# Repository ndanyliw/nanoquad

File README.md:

nanoquad
========

A low cost quadcopter development platform

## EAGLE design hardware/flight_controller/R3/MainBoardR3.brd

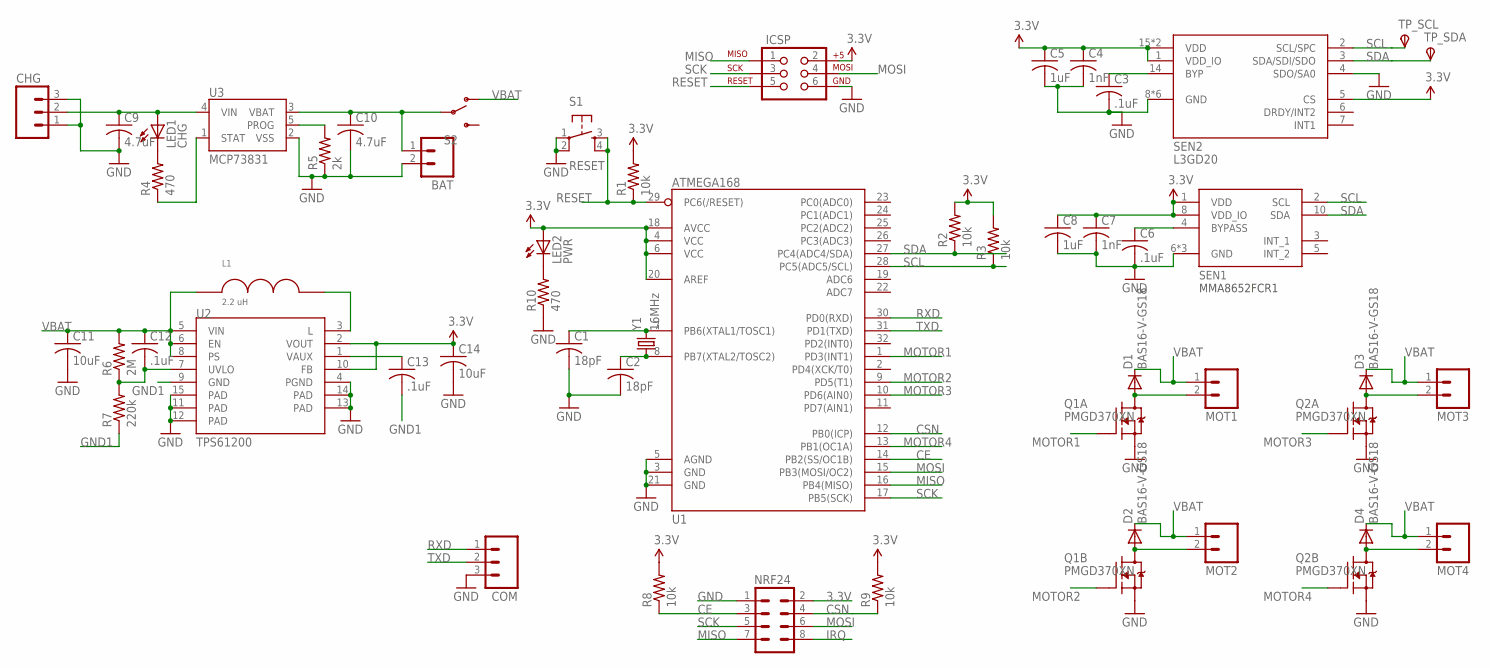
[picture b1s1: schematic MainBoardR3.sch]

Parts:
BAT: M02LOCK_LONGPADS; 1X02_LOCK_LONGPADS
C1, C2: 18pF; C0805
C3, C6, C12, C13: .1uF; C0805
C4, C7: 1nF; C0805
C5, C8: 1uF; C0805
C9, C10: 4.7uF; C0805
C11, C14: 10uF; C0805
CHG: M03LONGPADS; 1X03_LONGPADS
COM: M03LONGPADS; 1X03_LONGPADS
D1, D2, D3, D4: BAS16-V-GS18; SOT23
ICSP: AVR_SPI_PRG_62X3_LOCK; 2X3_LOCK
L1: 2.2 uH; 2518
LED1: CHG; LED-1206
LED2: PWR; LED-1206
MOT1, MOT2, MOT3, MOT4: M02LOCK_LONGPADS; 1X02_LOCK_LONGPADS
NRF24: M04X2; 2X4
Q1, Q2: PMGD370XN; SOT363_INFINEON
R1, R2, R3, R8, R9: 10k; 0805
R4, R10: 470; 0805
R5: 2k; 0805
R6: 2M; 0805
R7: 220k; 0805
S1: RESET; TACTILE_SWITCH_SMD
S2: SWITCH-SPST-SMD-A
SEN1: MMA8652FCR1; 10_PIN_DFN
SEN2: L3GD20; LGA-16
TP_SCL: TPSTP14SQ; TP14SQ
TP_SDA: TPSTP14SQ; TP14SQ
U1: ATMEGA168; TQFP32-08
U2: TPS61200; QFN-10_PAD
U3: MCP73831; SOT23-5
Y1: 16MHz; CRYSTAL-SMD-10.5X4.8-2PIN

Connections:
3.3V: C4.1, C5.1, C7.1, C8.1, C14.1, ICSP.2, LED2.A, NRF24.2, R1.2, R2.2, R3.2, R8.2, R9.2, SEN1.1 (VDD), SEN1.8 (VDD_IO), SEN2.1 (VDD_IO), SEN2.5 (CS), SEN2.15 (VDD), SEN2.16 (VDD), U1.4 (VCC), U1.6 (VCC), U1.18 (AVCC), U1.20 (AREF), U2.2 (VOUT), U2.10 (FB)
BAT+: BAT.1, C10.1, S2.2, U3.3 (VBAT)
CE: NRF24.3, R8.1, U1.14 (PB2(SS/OC1B))
CSN: NRF24.4, R9.1, U1.12 (PB0(ICP))
GND: BAT.2, C1.2, C2.2, C3.2, C4.2, C5.2, C6.2, C7.2, C8.2, C9.2, C10.2, C11.2, C14.2, CHG.1, CHG.3, COM.3, ICSP.6, NRF24.1, Q1.1 (S), Q1.4 (S), Q2.1 (S), Q2.4 (S), R5.1, R10.1, S1.1, S1.2, SEN1.6 (GND), SEN1.7 (GND), SEN1.9 (GND), SEN2.4 (SDO/SA0), SEN2.8 (GND), SEN2.9 (GND), SEN2.10 (GND), SEN2.11 (GND), SEN2.12 (GND), SEN2.13 (GND), U1.3 (GND), U1.5 (AGND), U1.21 (GND), U2.4 (PGND), U2.11 (PAD), U2.12 (PAD), U2.13 (PAD), U2.14 (PAD), U2.15 (PAD), U3.2 (VSS)
GND1: C13.2, R7.1, U2.9 (GND)
IRQ: NRF24.8
MISO: ICSP.1, NRF24.7, U1.16 (PB4(MISO))
MOSI: ICSP.4, NRF24.6, U1.15 (PB3(MOSI/OC2))
MOT1-: D1.1 (A), MOT1.2, Q1.6 (D)
MOT2-: D2.1 (A), MOT2.2, Q1.3 (D)
MOT3-: D3.1 (A), MOT3.2, Q2.6 (D)
MOT4-: D4.1 (A), MOT4.2, Q2.3 (D)
MOTOR1: Q1.2 (G), U1.1 (PD3(INT1))
MOTOR2: Q1.5 (G), U1.9 (PD5(T1))
MOTOR3: Q2.2 (G), U1.10 (PD6(AIN0))
MOTOR4: Q2.5 (G), U1.13 (PB1(OC1A))
unnamed: C3.1, SEN2.14 (BYP)
unnamed: C1.1, U1.7 (PB6(XTAL1/TOSC1)), Y1.P$2 (2)
unnamed: C2.1, U1.8 (PB7(XTAL2/TOSC2)), Y1.P$1 (1)
unnamed: LED1.C, R4.2
unnamed: C6.1, SEN1.4 (BYPASS)
unnamed: R4.1, U3.1 (STAT)
unnamed: R5.2, U3.5 (PROG)
unnamed: C13.1, U2.1 (VAUX)
unnamed: C12.2, R6.1, R7.2, U2.7 (UVLO)
unnamed: LED2.C, R10.2
unnamed: L1.P$2 (2), U2.3 (L)
RESET: ICSP.5, R1.1, S1.3, S1.4, U1.29 (PC6(/RESET))
RXD: COM.1, U1.30 (PD0(RXD))
SCK: ICSP.3, NRF24.5, U1.17 (PB5(SCK))
SCL: R3.1, SEN1.2 (SCL), SEN2.2 (SCL/SPC), TP_SCL.TP, U1.28 (PC5(ADC5/SCL))
SDA: R2.1, SEN1.10 (SDA), SEN2.3 (SDA/SDI/SDO), TP_SDA.TP, U1.27 (PC4(ADC4/SDA))
TXD: COM.2, U1.31 (PD1(TXD))
VBAT: C11.1, C12.1, D1.3 (C), D2.3 (C), D3.3 (C), D4.3 (C), L1.P$1 (1), MOT1.1, MOT2.1, MOT3.1, MOT4.1, R6.2, S2.1 (O), U2.5 (VIN), U2.6 (EN), U2.8 (PS)
VIN: C9.1, CHG.2, LED1.A, U3.4 (VIN)

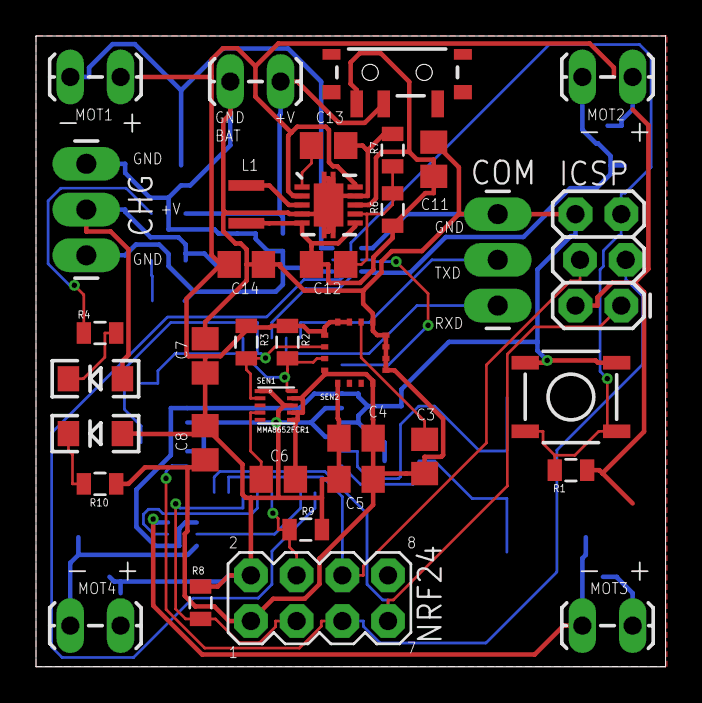
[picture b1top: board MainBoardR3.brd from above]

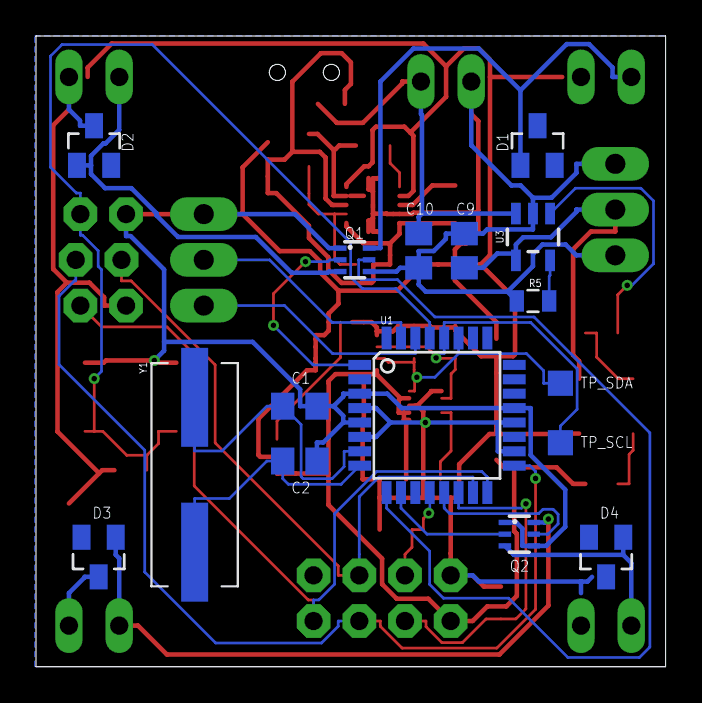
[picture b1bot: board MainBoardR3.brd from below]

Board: 2 copper layers, 35.0 x 35.0 mm, 52 parts (16 on the bottom side), 35 nets.

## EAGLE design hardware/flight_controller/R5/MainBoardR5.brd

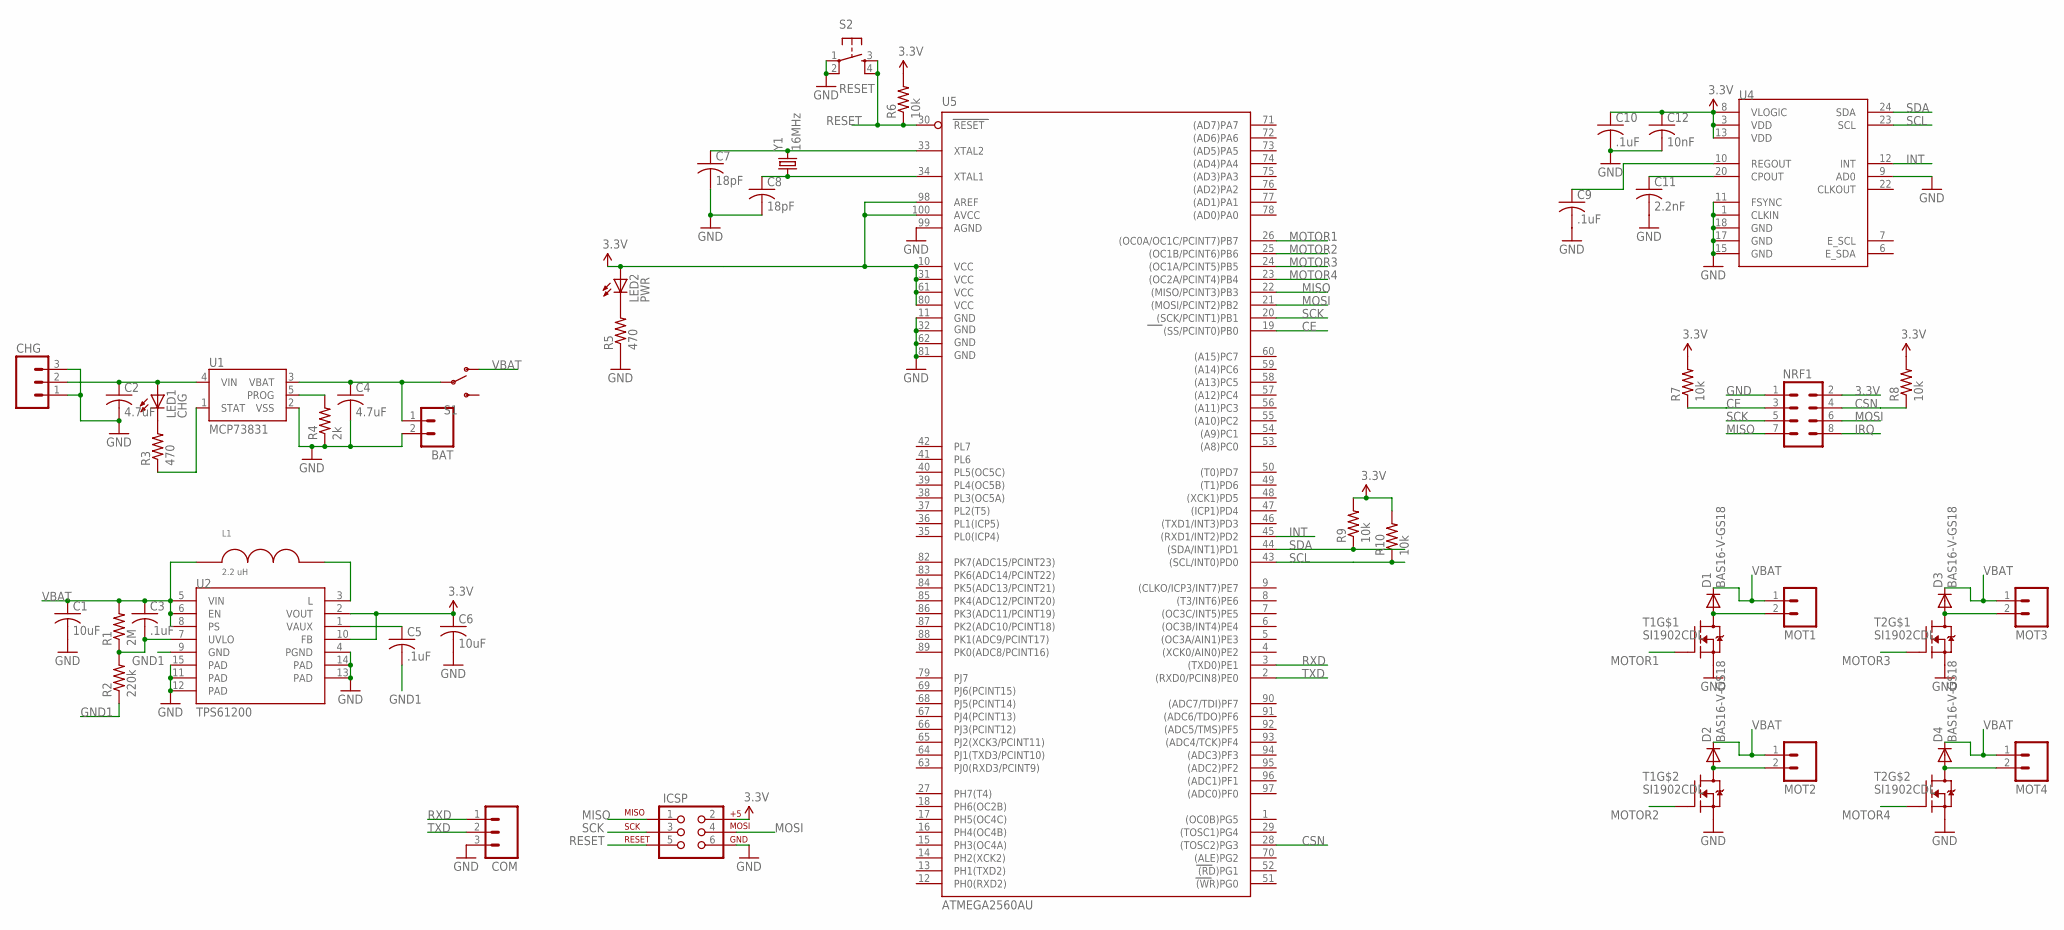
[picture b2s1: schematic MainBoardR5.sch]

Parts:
BAT: M02LOCK_LONGPADS; 1X02_LOCK_LONGPADS
C1, C6: 10uF; C0805
C2, C4: 4.7uF; C0805
C3, C5, C9, C10: .1uF; C0805
C7, C8: 18pF; C0805
C11: 2.2nF; C0805
C12: 10nF; C0805
CHG: M03LONGPADS; 1X03_LONGPADS
COM: M03LONGPADS; 1X03_LONGPADS
D1, D2, D3, D4: BAS16-V-GS18; SOT23
ICSP: AVR_SPI_PRG_62X3_LOCK; 2X3_LOCK
L1: 2.2 uH; 2518
LED1: CHG; LED-1206
LED2: PWR; LED-1206
MOT1, MOT2, MOT3, MOT4: M02LOCK_LONGPADS; 1X02_LOCK_LONGPADS
NRF1: M04X2; 2X4
R1: 2M; 0805
R2: 220k; 0805
R3, R5: 470; 0805
R4: 2k; 0805
R6, R7, R8, R9, R10: 10k; 0805
S1: SWITCH-SPST-SMD-A
S2: RESET; TACTILE_SWITCH_SMD
T1, T2: SI1902CDL; SOT363_INFINEON
U1: MCP73831; SOT23-5
U2: TPS61200; QFN-10_PAD
U4: MPU-9150QFN-24-NP; QFN-24-NP
U5: ATMEGA2560AU; TQFP100
Y1: 16MHz; CRYSTAL-SMD-5X3

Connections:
3.3V: C6.1, C10.1, C12.1, ICSP.2, LED2.A, NRF1.2, R6.2, R7.2, R8.2, R9.2, R10.2, U2.2 (VOUT), U2.10 (FB), U4.3 (VDD), U4.8 (VLOGIC), U4.13 (VDD), U5.10 (VCC), U5.31 (VCC1), U5.61 (VCC2), U5.80 (VCC3), U5.98 (AREF), U5.100 (AVCC)
BAT+: BAT.1, C4.1, S1.2, U1.3 (VBAT)
CE: NRF1.3, R7.1, U5.19 ((SS/PCINT0)PB0)
CSN: NRF1.4, R8.1, U5.28 ((TOSC2)PG3)
GND: BAT.2, C1.2, C2.2, C4.2, C6.2, C7.2, C8.2, C9.2, C10.2, C11.2, C12.2, CHG.1, CHG.3, COM.3, ICSP.6, NRF1.1, R4.1, R5.1, S2.1, S2.2, T1.1 (S), T1.4 (S), T2.1 (S), T2.4 (S), U1.2 (VSS), U2.4 (PGND), U2.11 (PAD), U2.12 (PAD), U2.13 (PAD), U2.14 (PAD), U2.15 (PAD), U4.1 (CLKIN), U4.9 (AD0), U4.11 (FSYNC), U4.15 (GND), U4.17 (GND), U4.18 (GND), U5.11 (GND), U5.32 (GND1), U5.62 (GND2), U5.81 (GND3), U5.99 (AGND)
GND1: C5.2, R2.1, U2.9 (GND)
INT: U4.12 (INT), U5.45 ((RXD1/INT2)PD2)
IRQ: NRF1.8
MISO: ICSP.1, NRF1.7, U5.22 ((MISO/PCINT3)PB3)
MOSI: ICSP.4, NRF1.6, U5.21 ((MOSI/PCINT2)PB2)
MOT1-: D1.1 (A), MOT1.2, T1.6 (D)
MOT2-: D2.1 (A), MOT2.2, T1.3 (D)
MOT3-: D3.1 (A), MOT3.2, T2.6 (D)
MOT4-: D4.1 (A), MOT4.2, T2.3 (D)
MOTOR1: T1.2 (G), U5.26 ((OC0A/OC1C/PCINT7)PB7)
MOTOR2: T1.5 (G), U5.25 ((OC1B/PCINT6)PB6)
MOTOR3: T2.2 (G), U5.24 ((OC1A/PCINT5)PB5)
MOTOR4: T2.5 (G), U5.23 ((OC2A/PCINT4)PB4)
unnamed: C7.1, U5.33 (XTAL2), Y1.3 (2)
unnamed: C8.1, U5.34 (XTAL1), Y1.1
unnamed: C11.1, U4.20 (CPOUT)
unnamed: LED1.C, R3.2
unnamed: C9.1, U4.10 (REGOUT)
unnamed: R3.1, U1.1 (STAT)
unnamed: R4.2, U1.5 (PROG)
unnamed: C5.1, U2.1 (VAUX)
unnamed: C3.2, R1.1, R2.2, U2.7 (UVLO)
unnamed: LED2.C, R5.2
unnamed: L1.P$2 (2), U2.3 (L)
RESET: ICSP.5, R6.1, S2.3, S2.4, U5.30 (RESET)
RXD: COM.1, U5.3 ((TXD0)PE1)
SCK: ICSP.3, NRF1.5, U5.20 ((SCK/PCINT1)PB1)
SCL: R10.1, U4.23 (SCL), U5.43 ((SCL/INT0)PD0)
SDA: R9.1, U4.24 (SDA), U5.44 ((SDA/INT1)PD1)
TXD: COM.2, U5.2 ((RXD0/PCIN8)PE0)
VBAT: C1.1, C3.1, D1.3 (C), D2.3 (C), D3.3 (C), D4.3 (C), L1.P$1 (1), MOT1.1, MOT2.1, MOT3.1, MOT4.1, R1.2, S1.1 (O), U2.5 (VIN), U2.6 (EN), U2.8 (PS)
VIN: C2.1, CHG.2, LED1.A, U1.4 (VIN)

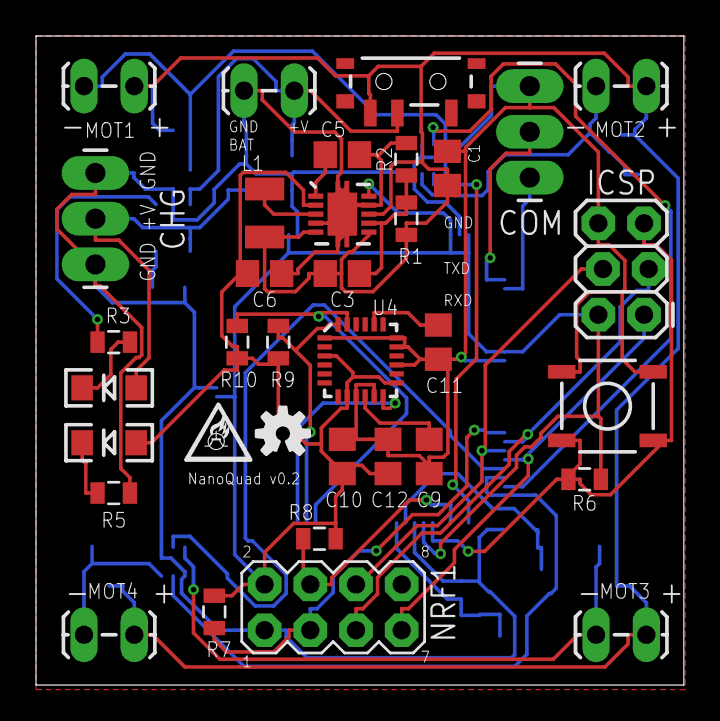
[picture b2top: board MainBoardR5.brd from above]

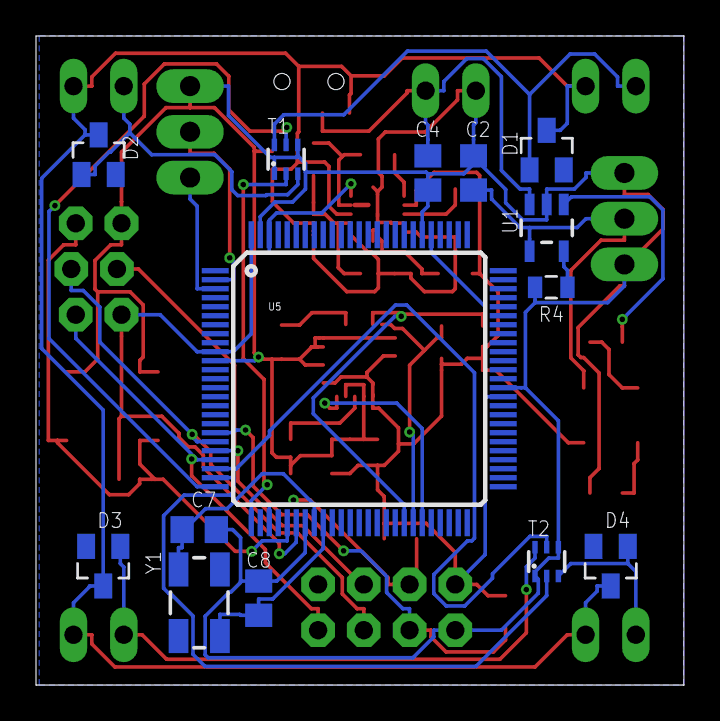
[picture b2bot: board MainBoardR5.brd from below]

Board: 2 copper layers, 36.0 x 36.1 mm, 49 parts (14 on the bottom side), 36 nets.

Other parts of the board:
U$1: BURNT_TRANSISTORS_XSM
U$2: OSHW-LOGO-S

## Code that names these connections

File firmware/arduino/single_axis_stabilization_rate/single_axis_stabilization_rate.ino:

/*
The MIT License (MIT)

Copyright (c) 2014 Ned Danyliw

Permission is hereby granted, free of charge, to any person obtaining a copy
of this software and associated documentation files (the "Software"), to deal
in the Software without restriction, including without limitation the rights
to use, copy, modify, merge, publish, distribute, sublicense, and/or sell
copies of the Software, and to permit persons to whom the Software is
furnished to do so, subject to the following conditions:

The above copyright notice and this permission notice shall be included in all
copies or substantial portions of the Software.

THE SOFTWARE IS PROVIDED "AS IS", WITHOUT WARRANTY OF ANY KIND, EXPRESS OR
IMPLIED, INCLUDING BUT NOT LIMITED TO THE WARRANTIES OF MERCHANTABILITY,
FITNESS FOR A PARTICULAR PURPOSE AND NONINFRINGEMENT. IN NO EVENT SHALL THE
AUTHORS OR COPYRIGHT HOLDERS BE LIABLE FOR ANY CLAIM, DAMAGES OR OTHER
LIABILITY, WHETHER IN AN ACTION OF CONTRACT, TORT OR OTHERWISE, ARISING FROM,
OUT OF OR IN CONNECTION WITH THE SOFTWARE OR THE USE OR OTHER DEALINGS IN THE
SOFTWARE.
*/

/*
This program runs a single axis stabilization algorithm on the quadcopter.
It only stabilizes in pitch.
*/

#include <stdlib.h>
#include <avr/io.h>
#include <avr/interrupt.h>
#include <avr/pgmspace.h>
#include <util/delay.h>
#include <math.h>  //include libm

#define UART_BAUD_RATE 57600
#include "mpu6050.h"
#include "mpu6050registers.h"
#include "i2cmaster.h"

#include <Wire.h>
#include "PID_v1.h"


#define MOTOR1 3
#define MOTOR2 5
#define MOTOR3 6
#define MOTOR4 9

#define XGYRO_OFFSET 16
#define YGYRO_OFFSET 16
#define ZGYRO_OFFSET 11


long *ptr = 0;
double qw = 1.0f;
double qx = 0.0f;
double qy = 0.0f;
double qz = 0.0f;
double roll = 0.0f;
double pitch = 0.0f;
double yaw = 0.0f;

double pitch_deg, roll_deg, yaw_deg;

int16_t mx = 0;
int16_t my = 0;
int16_t mz = 0;

int16_t gx, gy, gz;

double pitch_setpoint = 0.0f;
uint8_t thrust = 200;

int motor1, motor2, motor3, motor4;

double pitch_error;
double pitch_error_sum = 0.0f;

double pitch_rate;
double gyro_pitch_rate;

double kp_pitch_att = 4;
double ki_pitch_att = 0.05;
double kd_pitch_att = 0.0;

double kp_pitch_rate = .4;
double ki_pitch_rate = 0.005;
double kd_pitch_rate = 0.0;

double error;

long last = 0;
long time_elapsed;

//create PID controllers for pitch
PID pitch_pid_attitude(&pitch_deg, &pitch_error, &pitch_setpoint, kp_pitch_att, ki_pitch_att, kd_pitch_att, DIRECT);
PID pitch_pid_rate(&gyro_pitch_rate, &pitch_rate, &pitch_error, kp_pitch_rate, ki_pitch_rate, kd_pitch_rate, DIRECT);

void setup() {
    //set up 8 bit Fast PWM
    TCCR2A = _BV(COM2A1) | _BV(COM2B1) | _BV(WGM21) | _BV(WGM20);
    TCCR1A = _BV(COM1A1) | _BV(COM1B1) | _BV(WGM10);
    TCCR1B = _BV(WGM12) | _BV(CS11) | _BV(CS10);

    //zero motors
    analogWrite(MOTOR1, 0);
    analogWrite(MOTOR3, 0);
    analogWrite(MOTOR2, 0);
    analogWrite(MOTOR4, 0);

    Wire.begin();
    Serial.begin(UART_BAUD_RATE);

    //init mpu6050
    mpu6050_init();
    delay(50);

    mpu6050_setXGyroOffset(XGYRO_OFFSET);
    mpu6050_setYGyroOffset(YGYRO_OFFSET);
    mpu6050_setZGyroOffset(ZGYRO_OFFSET);

    mpu6050_dmpInitialize();
    mpu6050_dmpEnable();
    delay(10);

    //get gyro reading
    mpu6050_getRawGyro(&gx, &gy, &gz);

    //initialize PID
    pitch_pid_attitude.SetSampleTime(50);
    pitch_pid_attitude.SetOutputLimits(-180, 180);

    pitch_pid_rate.SetSampleTime(50);
    pitch_pid_rate.SetOutputLimits(-255+thrust, 255-thrust);

    delay(5000);
    last = millis();
    pitch_deg = -pitch * 180.0/3.1416;
    gyro_pitch_rate = (gx - XGYRO_OFFSET)/MPU6050_GYRO_LSB_2000;
    pitch_pid_attitude.SetMode(AUTOMATIC);
    pitch_pid_rate.SetMode(AUTOMATIC);
}

void loop() {
    time_elapsed = millis();
    if(mpu6050_getQuaternionWait(&qw, &qx, &qy, &qz)) {
        mpu6050_getRollPitchYaw(qw, qx, qy, qz, &roll, &pitch, &yaw);
    }
    // read_compass(&mx, &my, &mz);
    // uart_puts("hello world4!\n");

    mpu6050_getRawGyro(&gx, &gy, &gz);
    pitch_deg = -pitch * 180.0/3.1416;
    gyro_pitch_rate = (gx - XGYRO_OFFSET)/MPU6050_GYRO_LSB_2000;

    // error = pitch_setpoint - pitch;
    // pitch_error_sum += error * (millis() - last)/1000.0;
    // pitch_error = kp_pitch*error + ki_pitch * pitch_error_sum;
    // last = millis();

    pitch_pid_attitude.Compute();
    pitch_pid_rate.Compute();

    //assign values to motors
    motor1 = thrust + pitch_rate;
    motor2 = thrust + pitch_rate;
    motor3 = thrust - pitch_rate;
    motor4 = thrust - pitch_rate;

    //handle overflow
    if (motor1 < 0) {
        motor1 = 0;
    } else if (motor1 > 255) {
        motor1 = 255;
    }

    if (motor2 < 0) {
        motor2 = 0;
    } else if (motor2 > 255) {
        motor2 = 255;
    }

    if (motor3 < 0) {
        motor3 = 0;
    } else if (motor3 > 255) {
        motor3 = 255;
    }

    if (motor4 < 0) {
        motor4 = 0;
    } else if (motor4 > 255) {
        motor4 = 255;
    }

    // analogWrite(MOTOR1, 0);
    // analogWrite(MOTOR3, 0);
    // analogWrite(MOTOR2, 0);
    // analogWrite(MOTOR4, 0);

    // if (millis() - last > 500) {
    //     Serial.print("Pitch - ");
    //     Serial.println(pitch_deg);
    //     Serial.print("Pitch Rate - ");
    //     Serial.println(gyro_pitch_rate);
    //     Serial.print("Motor 1 - ");
    //     Serial.println(motor1);
    //     Serial.print("Motor 3 - ");
    //     Serial.println(motor3);
    //     Serial.println(millis() - time_elapsed);

    //     last = millis();
    // }

    //update motors
    analogWrite(MOTOR1, motor1);
    analogWrite(MOTOR3, motor3);
    analogWrite(MOTOR2, motor2);
    analogWrite(MOTOR4, motor4);

    // delay(3);
}

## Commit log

2014-05-21 Added all current source files and hardware designs. Also added a hardware specific license file.
2014-05-21 Added CAD files for frame
2014-07-15 Added BOM for Quadcopter parts

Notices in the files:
parts and their libraries:
SparkFun: Licensing: CC v3.0 Share-Alike You are welcome to use this library for commercial purposes.
